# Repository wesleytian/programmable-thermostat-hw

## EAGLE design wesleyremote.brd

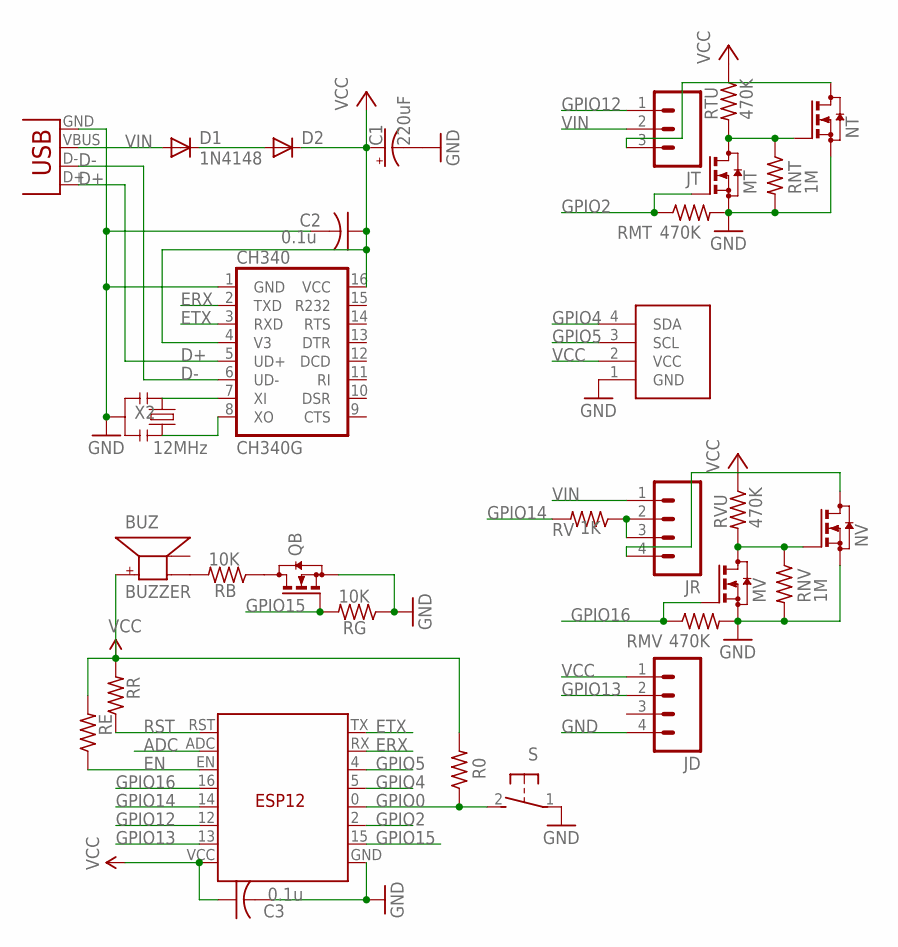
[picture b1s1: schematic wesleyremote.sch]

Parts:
BUZ: BUZZER; SMT-8585-BUZZER
C1: 220uF; EIA3528-KIT
C2, C3: 0.1u; C0603K
CH340: CH340G; SO16
D1: 1N4148; MINIMELF
D2: DIODE-MINIMELF; MINIMELF
ESP12: ESP12ESPWES; ESP12_WES
JD: M04DHT; 1X04_DHT_RFRX
JR: M04RFRX; 1X04_RFRX
JT: M03RFTX; 1X03_RFTX
MT: AO3400; SOT23
MV: AO3400; SOT23
NT: AO3400; SOT23
NV: AO3400; SOT23
QB: AO3400; SOT23
R0: R-US_R0603; R0603
RB: 10K; R0603
RE: R-US_R0603; R0603
RG: 10K; R0603
RMT: 470K; R0603
RMV: 470K; R0603
RNT: 1M; R0603
RNV: 1M; R0603
RR: R-US_R0603; R0603
RTU: 470K; R0603
RV: 1K; R0603
RVU: 470K; R0603
S: 31-XX; B3F-31XX
U$1: SSD1306_OLED_I2C
X2: 12MHz; RESONATOR-SMD
X3: USBMICROB2; USB-MICROB2

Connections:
ADC: ESP12.ADC
D+: CH340.5 (UD+), X3.D+
D-: CH340.6 (UD-), X3.D-
EN: ESP12.EN, RE.1
ERX: CH340.2 (TXD), ESP12.RX
ETX: CH340.3 (RXD), ESP12.TX
GND: C1.C (-), C2.2, C3.2, CH340.1 (GND), ESP12.GND, JD.4, MT.2 (S), MV.2 (S), NT.2 (S), NV.2 (S), QB.2 (S), RG.1, RMT.2, RMV.2, RNT.2, RNV.2, S.1, U$1.1 (GND), X2.2, X3.GND
GPIO0: ESP12.0 (G0), R0.1, S.2 (S)
GPIO2: ESP12.2 (G2), MT.1 (G), RMT.1
GPIO4: ESP12.5 (G5), U$1.4 (SDA)
GPIO5: ESP12.4 (G4), U$1.3 (SCL)
GPIO12: ESP12.12 (G12), JT.1
GPIO13: ESP12.13 (G13), JD.2
GPIO14: ESP12.14 (G14), RV.2
GPIO15: ESP12.15 (G15), QB.1 (G), RG.2
GPIO16: ESP12.16 (G16), MV.1 (G), RMV.1
unnamed: BUZ.-, RB.2
unnamed: MV.3 (D), NV.1 (G), RNV.1, RVU.2
unnamed: MT.3 (D), NT.1 (G), RNT.1, RTU.2
unnamed: JT.3, NT.3 (D)
unnamed: D1.C, D2.A
unnamed: JR.2, JR.3, RV.1
unnamed: JR.4, NV.3 (D)
unnamed: QB.3 (D), RB.1
unnamed: CH340.7 (XI), X2.1
unnamed: CH340.8 (XO), X2.3
RST: ESP12.RST, RR.1
VCC: BUZ.+, C1.A (+), C2.1, C3.1, CH340.4 (V3), CH340.16 (VCC), D2.C, ESP12.VCC, JD.1, R0.2, RE.2, RR.2, RTU.1, RVU.1, U$1.2 (VCC)
VIN: D1.A, JR.1, JT.2, X3.VBUS

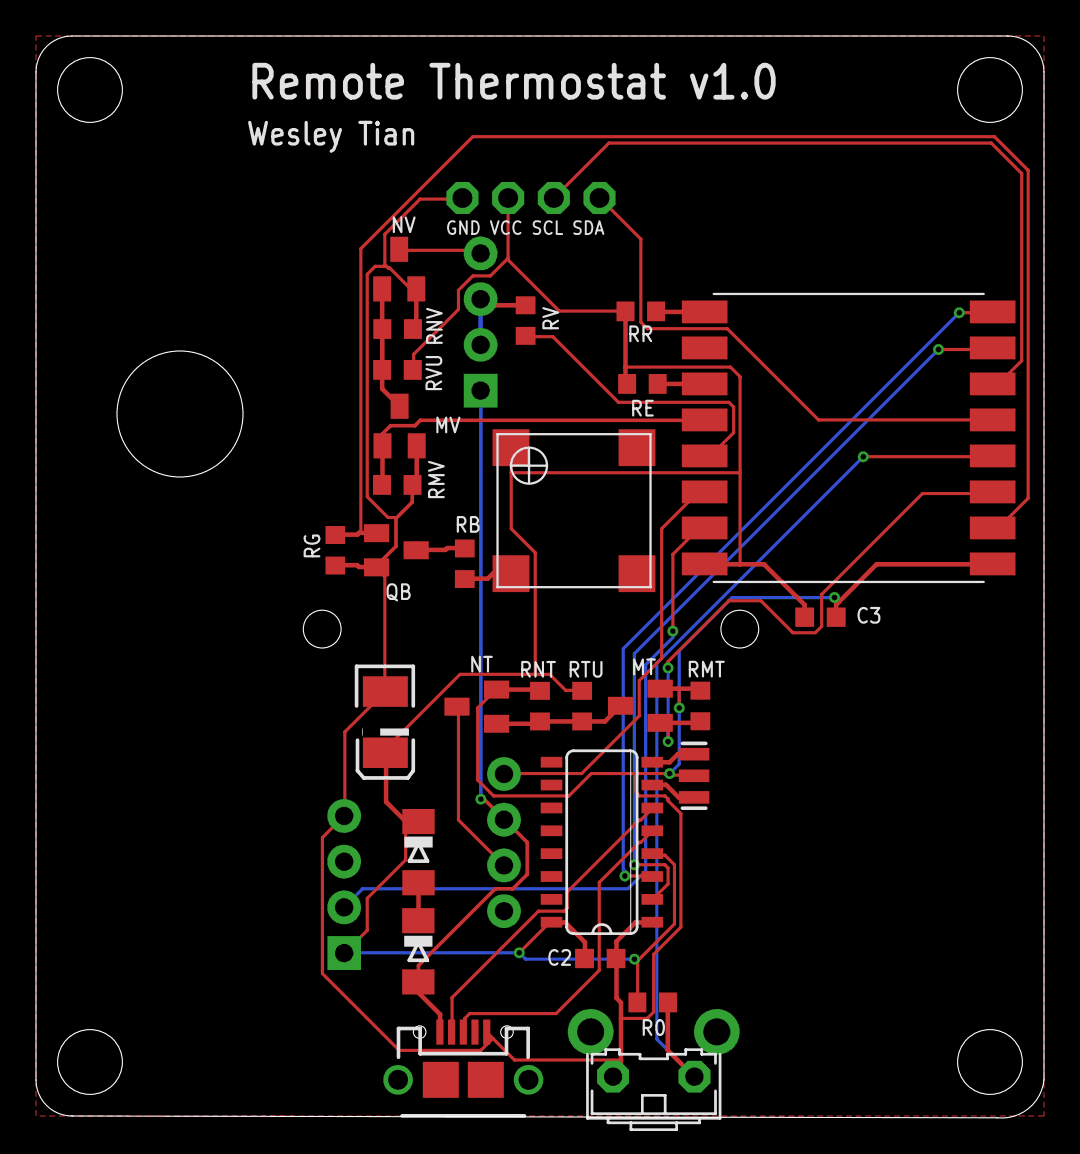
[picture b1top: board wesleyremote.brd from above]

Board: 2 copper layers, 56.0 x 60.1 mm, 32 parts (0 on the bottom side), 28 nets.

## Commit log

2016-10-01 brd, png, sch
2016-10-07 courtesy
